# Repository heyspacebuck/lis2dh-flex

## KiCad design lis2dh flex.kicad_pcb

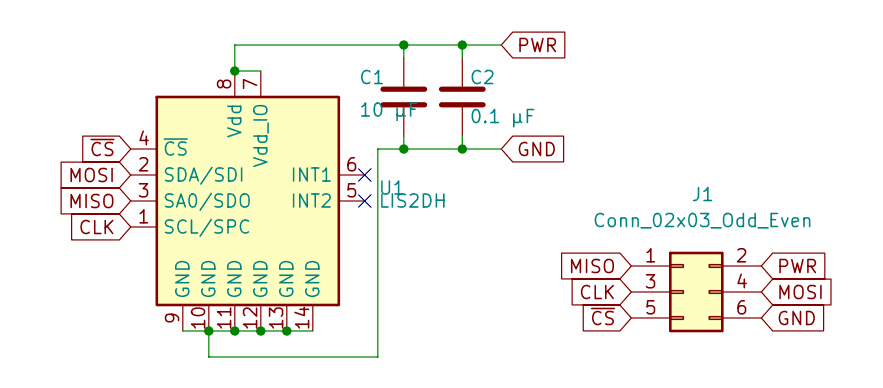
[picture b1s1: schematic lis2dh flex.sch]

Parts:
C1: 10 μF; C_0805_2012Metric_Pad1.15x1.40mm_HandSolder
C2: 0.1 μF; C_0805_2012Metric_Pad1.15x1.40mm_HandSolder
J1: Conn_02x03_Odd_Even; IDC-Header_2x03_P2.54mm_Vertical
U1: LIS2DH; LGA-14_2x2mm_P0.35mm_LayoutBorder3x4y

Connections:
CLK: J1.3, U1.1 (SCL/SPC)
GND: C1.1, C2.2, J1.6, U1.9 (GND), U1.10 (GND), U1.11 (GND), U1.12 (GND), U1.13 (GND), U1.14 (GND)
MISO: J1.1, U1.3 (SA0/SDO)
MOSI: J1.4, U1.2 (SDA/SDI)
PWR: C1.2, C2.1, J1.2, U1.7 (Vdd_IO), U1.8 (Vdd)
~CS: J1.5, U1.4 (~CS)

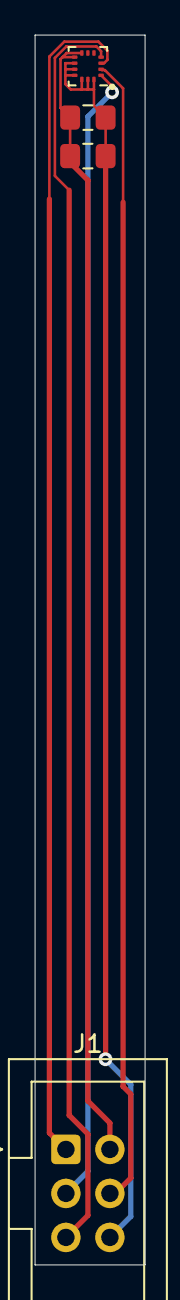
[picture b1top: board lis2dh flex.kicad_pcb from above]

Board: 2 copper layers, 6.4 x 71.0 mm, 4 parts (0 on the bottom side), 6 nets.

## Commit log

2020-09-01 Init commit
